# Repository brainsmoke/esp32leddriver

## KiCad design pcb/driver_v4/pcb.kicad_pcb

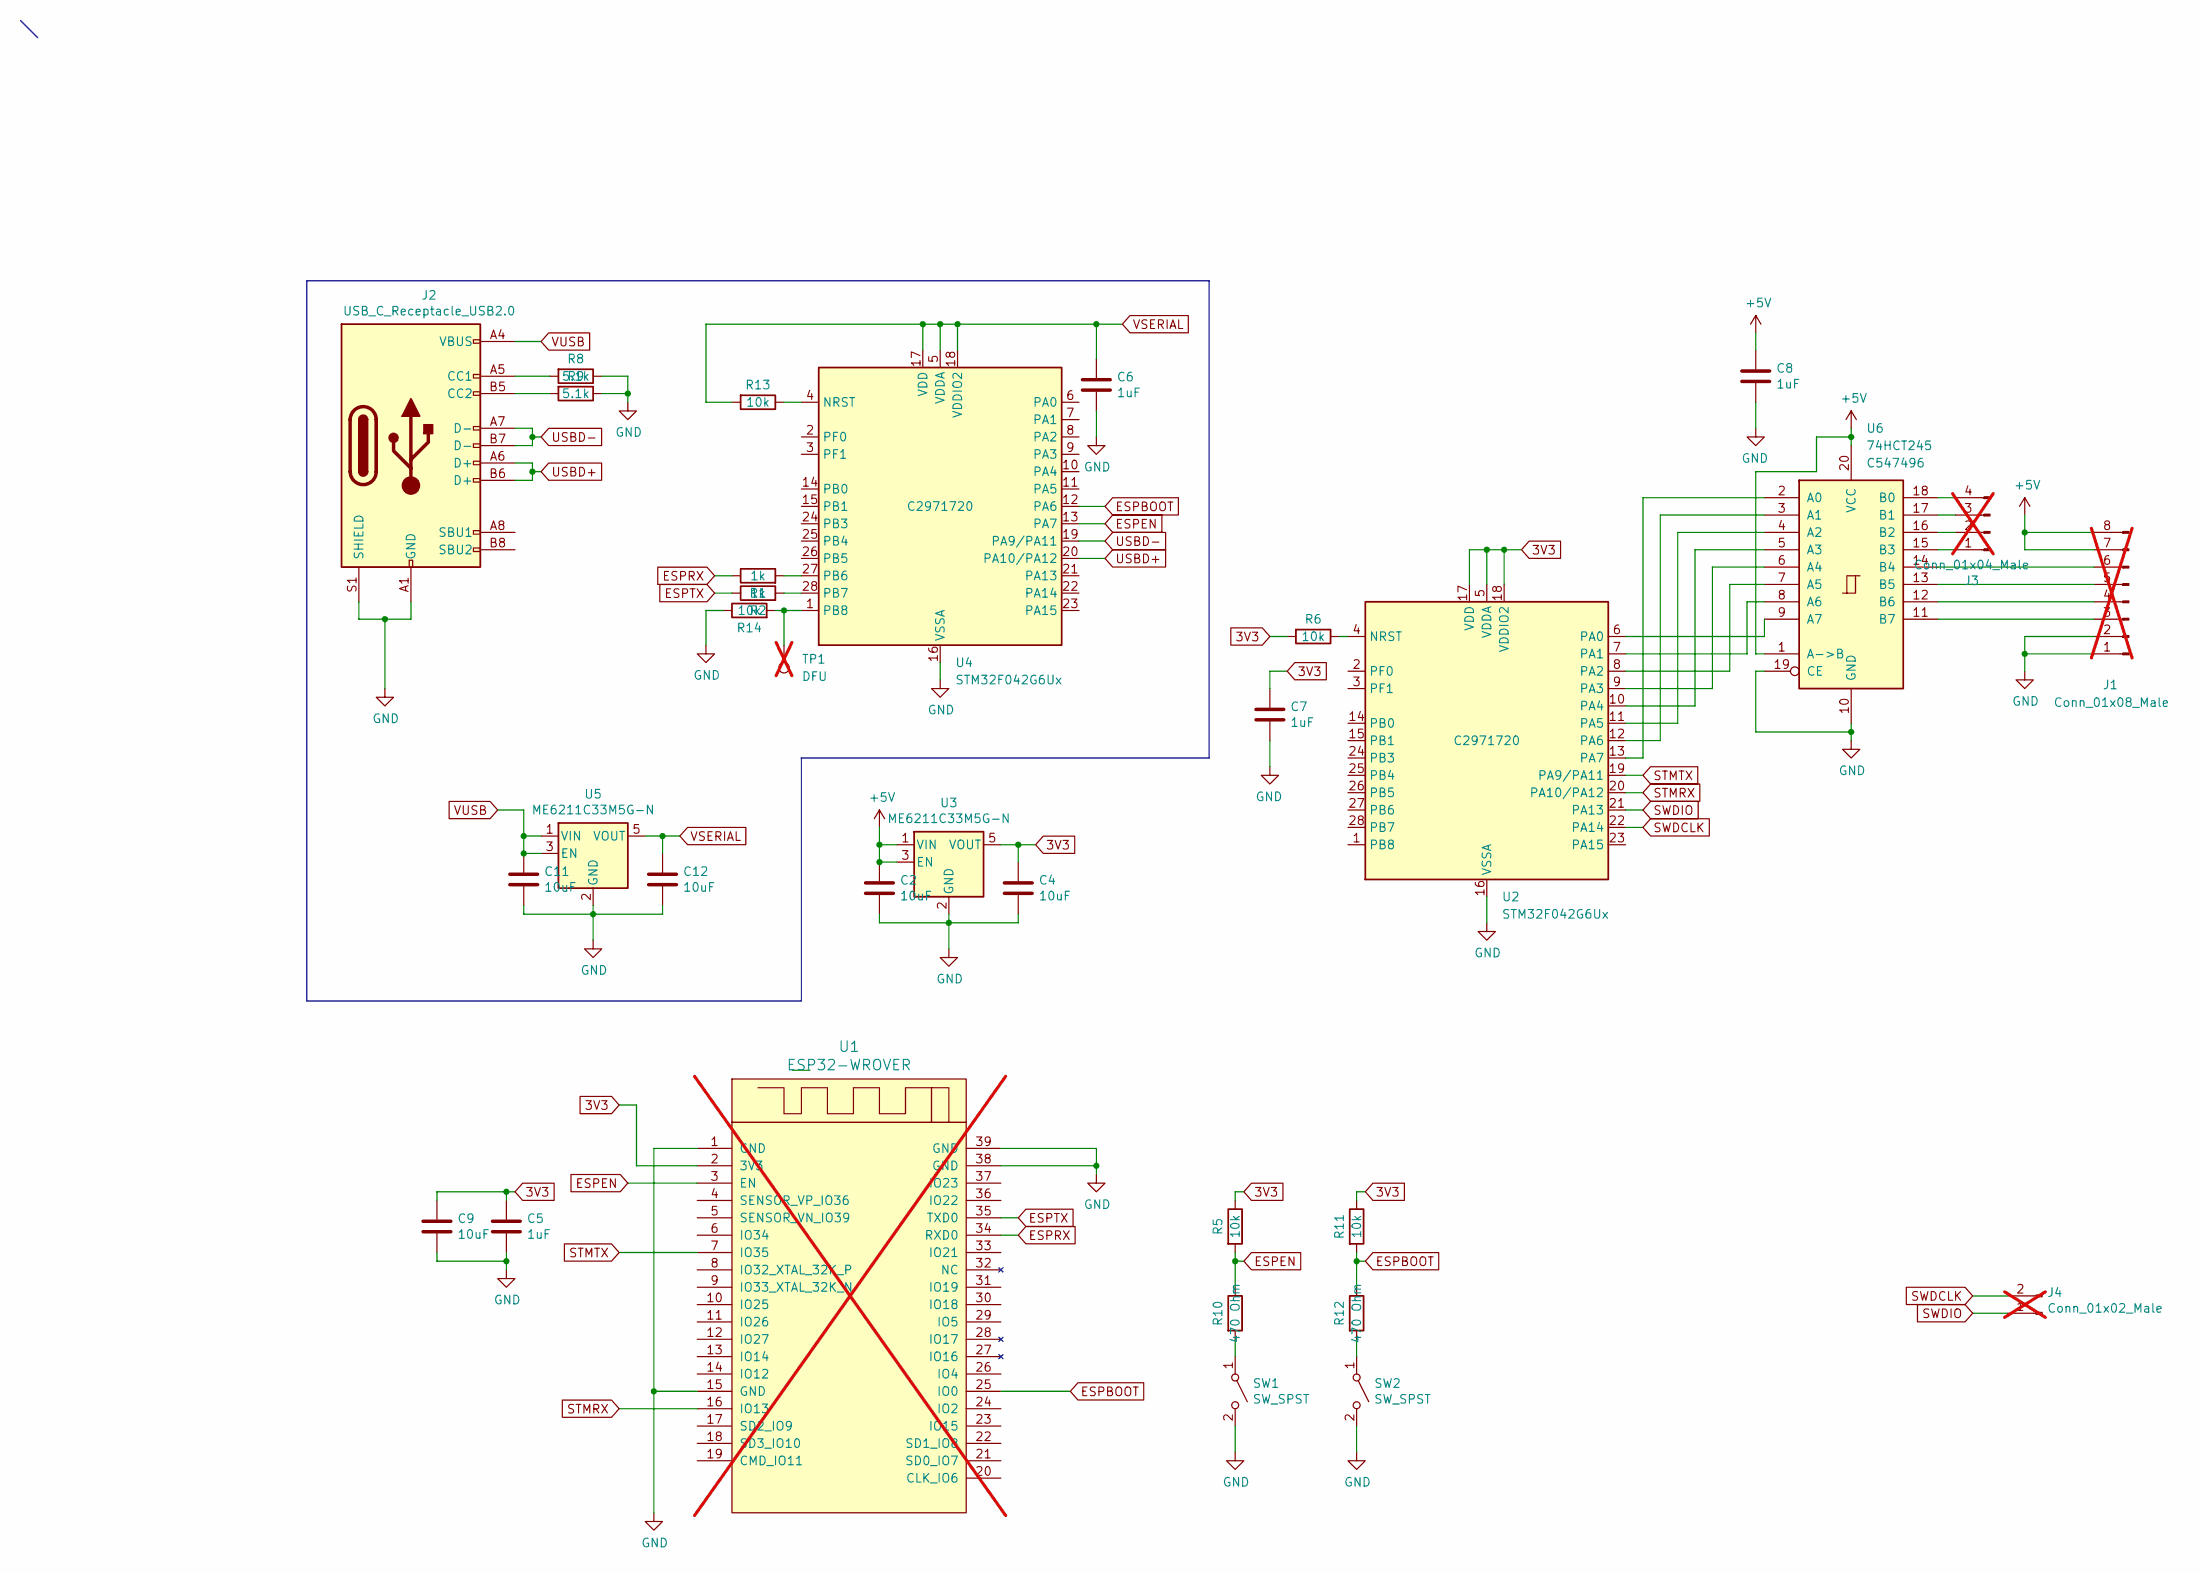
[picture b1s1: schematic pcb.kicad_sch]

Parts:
C2, C4, C9, C11, C12: 10uF; C_0603_1608Metric; LCSC C19702
C5, C6, C7, C8: 1uF; C_0402_1005Metric; LCSC C52923
J1: Conn_01x08_Male; PinHeader_1x08_P2.54mm_Vertical; not fitted
J2: USB_C_Receptacle_USB2.0; USB_C_Receptacle_HRO_TYPE-C-31-M-12; LCSC C165948
J3: Conn_01x04_Male; PinHeader_1x04_P2.54mm_Vertical; not fitted
J4: Conn_01x02_Male; PinHeader_1x02_P2.54mm_Vertical; not fitted
R1, R2: 1k; R_0402_1005Metric; LCSC C11702
R5, R6, R11, R13, R14: 10k; R_0402_1005Metric; LCSC C25744
R8, R9: 5.1k; R_0402_1005Metric; LCSC C25905
R10, R12: 470 Ohm; R_0402_1005Metric; LCSC C25117
SW1, SW2: SW_SPST; SW_Push_1P1T_NO_CK_KMR2; LCSC C318893
TP1: DFU; TestPoint_Pad_D1.0mm; not fitted
U1: ESP32-WROVER; XCVR_ESP32-WROVER; not fitted
U2, U4: STM32F042G6Ux; QFN-28_4x4mm_P0.5mm; LCSC C2971720
U3, U5: ME6211C33M5G-N; SOT-23-5; LCSC C82942
U6: 74HCT245; DHVQFN-20-1EP_2.5x4.5mm_P0.5mm_EP1x3mm; LCSC C547496

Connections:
3V3: C4.1, C5.1, C7.1, C9.1, R5.1, R6.2, R11.1, U1.2 (3V3), U2.5 (VDDA), U2.17 (VDD), U2.18 (VDDIO2), U3.5 (VOUT)
+5V: C2.1, C8.1, J1.7, J1.8, U3.1 (VIN), U3.3 (EN), U6.1 (A->B), U6.20 (VCC)
ESPBOOT: R11.2, R12.1, U1.25 (IO0), U4.12 (PA6)
ESPEN: R5.2, R10.1, U1.3 (EN), U4.13 (PA7)
ESPRX: R1.1, U1.34 (RXD0)
ESPTX: R2.1, U1.35 (TXD0)
GND: C2.2, C4.2, C5.2, C6.2, C7.2, C8.2, C9.2, C11.2, C12.2, J1.1, J1.2, J2.A1 (GND), J2.A12 (GND), J2.B1 (GND), J2.B12 (GND), J2.S1 (SHIELD), R8.1, R9.1, R14.1, SW1.2 (B), SW2.2 (B), U1.1 (GND), U1.15 (GND), U1.38 (GND), U1.39 (GND), U2.16 (VSSA), U3.2 (GND), U4.16 (VSSA), U5.2 (GND), U6.10 (GND), U6.19 (CE)
unnamed: J1.3, U6.11 (B7)
unnamed: J1.4, U6.12 (B6)
unnamed: J1.5, U6.13 (B5)
unnamed: J1.6, U6.14 (B4)
unnamed: J2.A5 (CC1), R8.2
unnamed: J2.B5 (CC2), R9.2
unnamed: J3.1, U6.15 (B3)
unnamed: J3.2, U6.16 (B2)
unnamed: J3.3, U6.17 (B1)
unnamed: J3.4, U6.18 (B0)
unnamed: R10.2, SW1.1 (A)
unnamed: R12.2, SW2.1 (A)
unnamed: R6.1, U2.4 (NRST)
unnamed: U2.6 (PA0), U6.9 (A7)
unnamed: U2.7 (PA1), U6.8 (A6)
unnamed: U2.8 (PA2), U6.7 (A5)
unnamed: U2.9 (PA3), U6.6 (A4)
unnamed: U2.10 (PA4), U6.5 (A3)
unnamed: U2.11 (PA5), U6.4 (A2)
unnamed: U2.12 (PA6), U6.3 (A1)
unnamed: U2.13 (PA7), U6.2 (A0)
unnamed: R13.1, U4.4 (NRST)
unnamed: R1.2, U4.27 (PB6)
unnamed: R2.2, U4.28 (PB7)
unnamed: R14.2, TP1.1, U4.1 (PB8)
STMRX: U1.16 (IO13), U2.20 (PA10/PA12)
STMTX: U1.7 (IO35), U2.19 (PA9/PA11)
SWDCLK: J4.2, U2.22 (PA14)
SWDIO: J4.1, U2.21 (PA13)
USBD+: J2.A6 (D+), J2.B6 (D+), U4.20 (PA10/PA12)
USBD-: J2.A7 (D-), J2.B7 (D-), U4.19 (PA9/PA11)
VSERIAL: C6.1, C12.1, R13.2, U4.5 (VDDA), U4.17 (VDD), U4.18 (VDDIO2), U5.5 (VOUT)
VUSB: C11.1, J2.A4 (VBUS), J2.A9 (VBUS), J2.B4 (VBUS), J2.B9 (VBUS), U5.1 (VIN), U5.3 (EN)

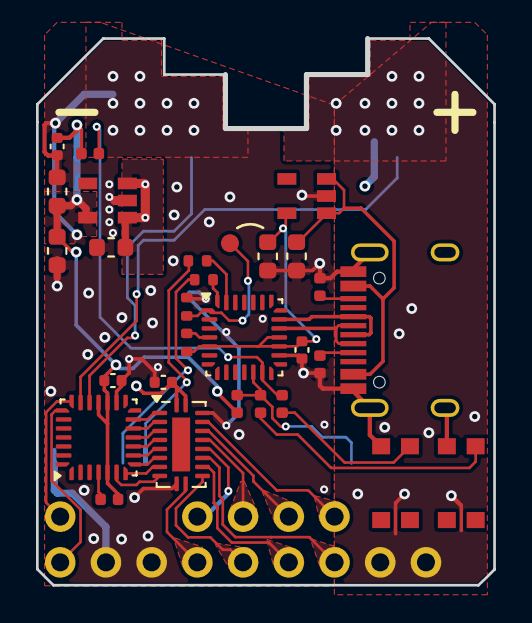
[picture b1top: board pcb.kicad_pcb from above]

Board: 4 copper layers, 25.4 x 30.4 mm, 33 parts (1 on the bottom side), 40 nets.

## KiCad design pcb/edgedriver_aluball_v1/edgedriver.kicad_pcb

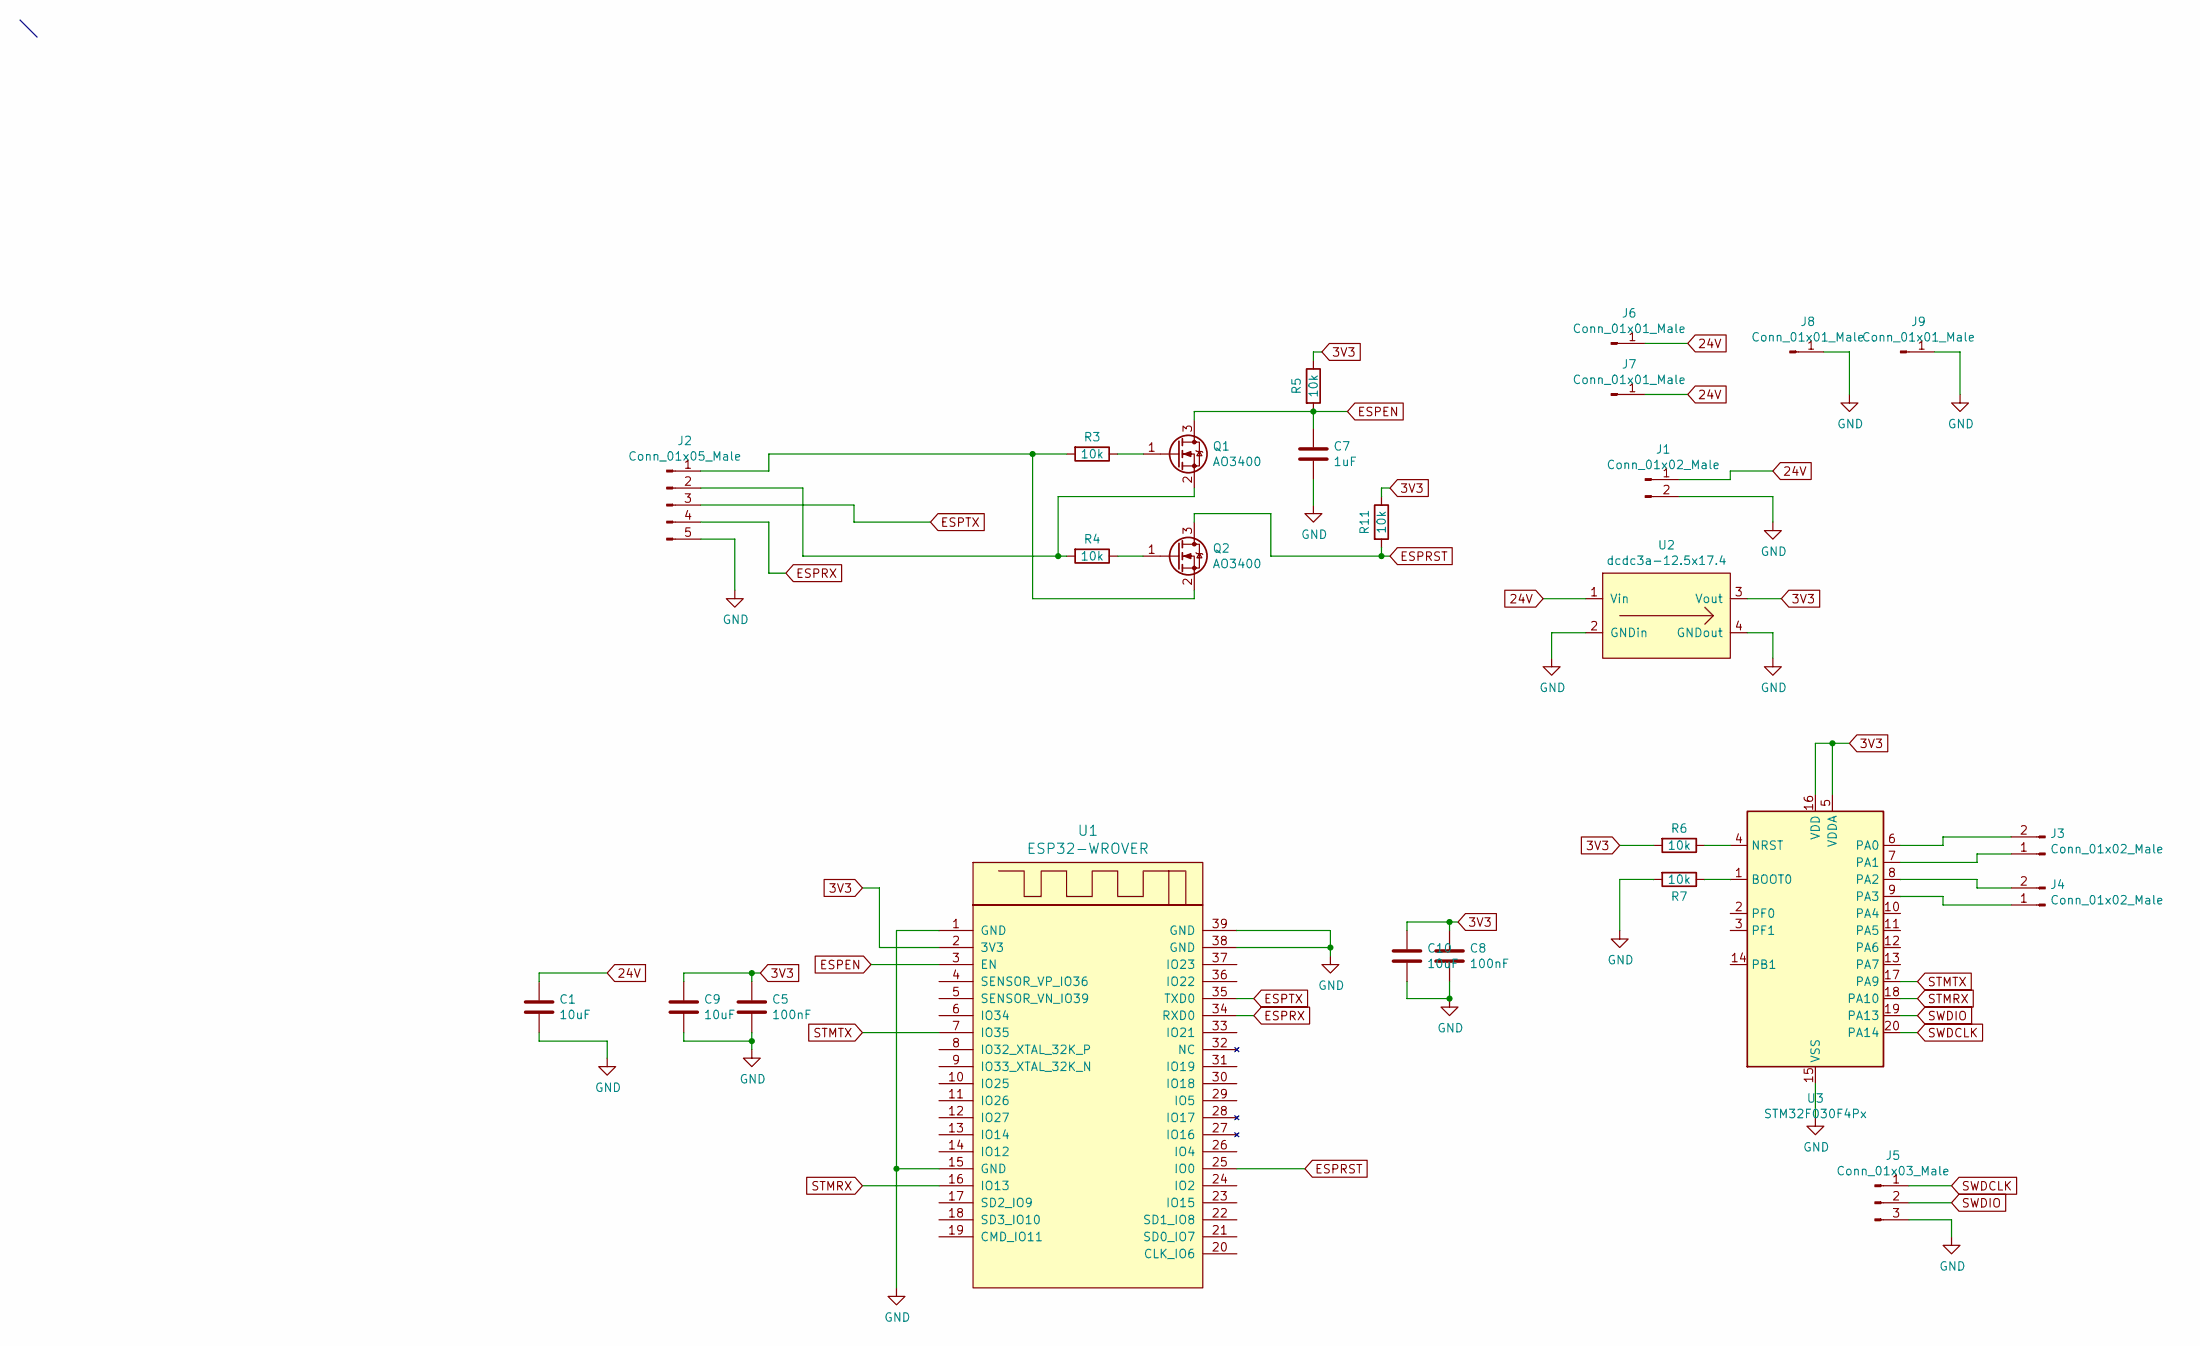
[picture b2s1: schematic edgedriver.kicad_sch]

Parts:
C1, C9, C10: 10uF; C_1206_3216Metric; LCSC C13585
C5, C8: 100nF; C_0402_1005Metric; LCSC C1525
C7: 1uF; C_0402_1005Metric; LCSC C52923
J1: Conn_01x02_Male; xt60-pcb
J2: Conn_01x05_Male; Molex_PicoBlade_53261-0571_1x05-1MP_P1.25mm_Horizontal; LCSC C225114
J3, J4: Conn_01x02_Male; PinHeader_1x02_P2.54mm_Vertical
J5: Conn_01x03_Male; PinHeader_1x03_P2.54mm_Vertical
J6, J7, J8, J9: Conn_01x01_Male; solderpad1
Q1, Q2: AO3400; SOT-23; LCSC C20917
R3, R4, R5, R6, R7, R11: 10k; R_0402_1005Metric; LCSC C25744
U1: ESP32-WROVER; XCVR_ESP32-WROVER; LCSC C701352
U2: dcdc3a-12.5x17.4
U3: STM32F030F4Px; TSSOP-20_4.4x6.5mm_P0.65mm; LCSC C89040

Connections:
3V3: C5.1, C8.1, C9.1, C10.1, R5.1, R6.2, R11.1, U1.2 (3V3), U2.3 (Vout), U3.5 (VDDA), U3.16 (VDD)
24V: C1.1, J1.1, J6.1, J7.1, U2.1 (Vin)
ESPEN: C7.1, Q1.3 (D), R5.2, U1.3 (EN)
ESPRST: Q2.3 (D), R11.2, U1.25 (IO0)
ESPRX: J2.4, U1.34 (RXD0)
ESPTX: J2.3, U1.35 (TXD0)
GND: C1.2, C5.2, C7.2, C8.2, C9.2, C10.2, J1.2, J2.5, J5.3, J8.1, J9.1, R7.2, U1.1 (GND), U1.15 (GND), U1.38 (GND), U1.39 (GND), U2.2 (GNDin), U2.4 (GNDout), U3.15 (VSS)
unnamed: J2.1, Q2.2 (S), R3.2
unnamed: J2.2, Q1.2 (S), R4.2
unnamed: J3.1, U3.7 (PA1)
unnamed: J3.2, U3.6 (PA0)
unnamed: J4.1, U3.9 (PA3)
unnamed: J4.2, U3.8 (PA2)
unnamed: Q1.1 (G), R3.1
unnamed: Q2.1 (G), R4.1
unnamed: R7.1, U3.1 (BOOT0)
unnamed: R6.1, U3.4 (NRST)
STMRX: U1.16 (IO13), U3.18 (PA10)
STMTX: U1.7 (IO35), U3.17 (PA9)
SWDCLK: J5.1, U3.20 (PA14)
SWDIO: J5.2, U3.19 (PA13)

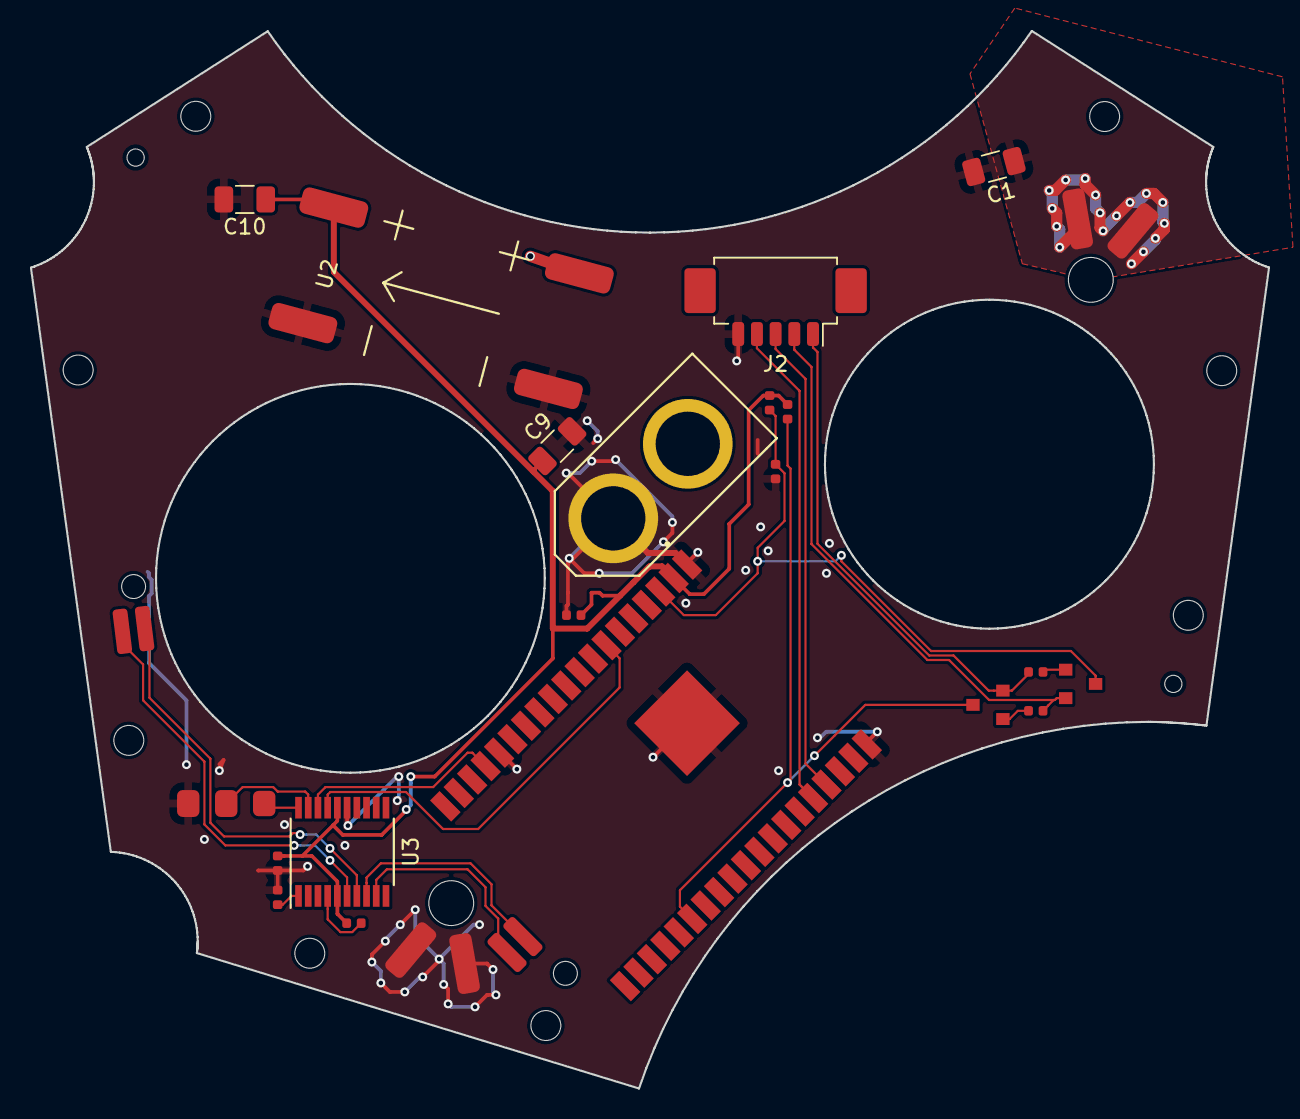
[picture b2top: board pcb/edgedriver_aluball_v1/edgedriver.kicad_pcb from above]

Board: 2 copper layers, 82.8 x 70.7 mm, 26 parts (0 on the bottom side), 21 nets.

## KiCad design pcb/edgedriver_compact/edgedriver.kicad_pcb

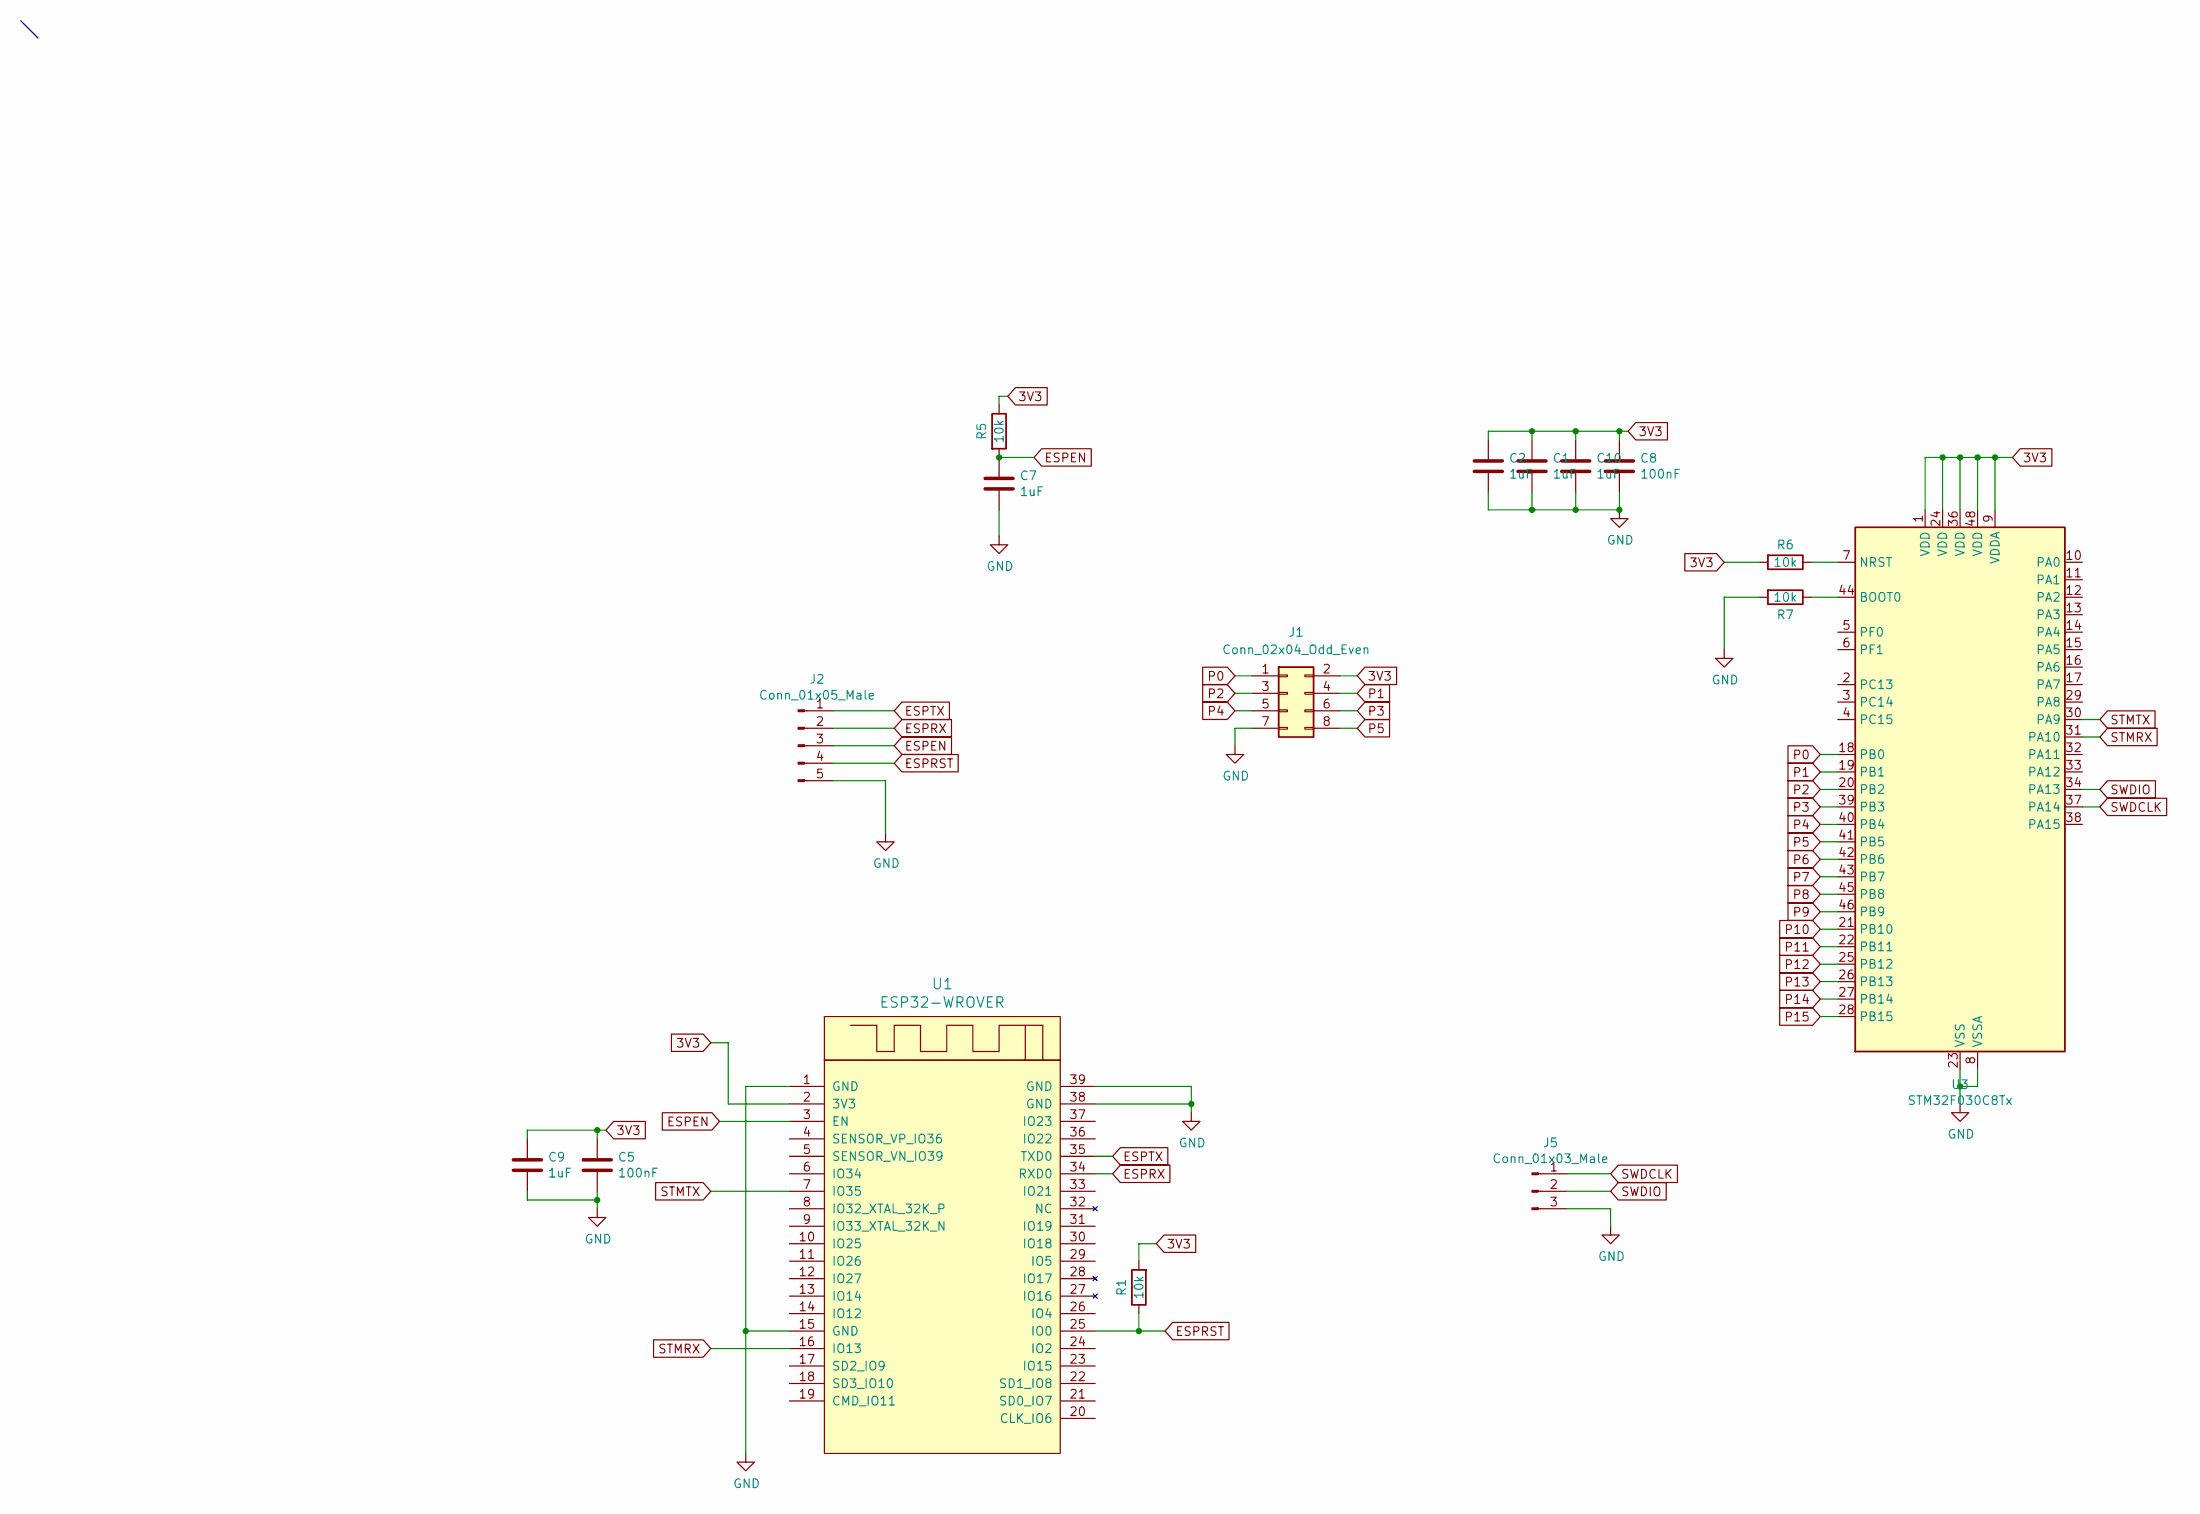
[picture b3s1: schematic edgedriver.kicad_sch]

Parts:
C1, C2, C7, C9, C10: 1uF; C_0402_1005Metric; LCSC C52923
C5, C8: 100nF; C_0402_1005Metric; LCSC C1525
J1: Conn_02x04_Odd_Even; PinSocket_2x04_P2.54mm_Vertical
J2: Conn_01x05_Male; Molex_PicoBlade_53261-0571_1x05-1MP_P1.25mm_Horizontal; LCSC C225114
J5: Conn_01x03_Male; PinHeader_1x03_P2.54mm_Vertical
R1, R5, R6, R7: 10k; R_0402_1005Metric; LCSC C25744
U1: ESP32-WROVER; XCVR_ESP32-WROVER; LCSC C701352
U3: STM32F030C8Tx; LQFP-48_7x7mm_P0.5mm; LCSC C23922

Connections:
3V3: C1.1, C2.1, C5.1, C8.1, C9.1, C10.1, J1.2, R1.2, R5.1, R6.2, U1.2 (3V3), U3.1 (VDD), U3.9 (VDDA), U3.24 (VDD), U3.36 (VDD), U3.48 (VDD)
ESPEN: C7.1, J2.3, R5.2, U1.3 (EN)
ESPRST: J2.4, R1.1, U1.25 (IO0)
ESPRX: J2.2, U1.34 (RXD0)
ESPTX: J2.1, U1.35 (TXD0)
GND: C1.2, C2.2, C5.2, C7.2, C8.2, C9.2, C10.2, J1.7, J2.5, J5.3, R7.2, U1.1 (GND), U1.15 (GND), U1.38 (GND), U1.39 (GND), U3.8 (VSSA), U3.23 (VSS), U3.35 (VSS), U3.47 (VSS)
unnamed: R7.1, U3.44 (BOOT0)
unnamed: R6.1, U3.7 (NRST)
P0: J1.1, U3.18 (PB0)
P1: J1.4, U3.19 (PB1)
P2: J1.3, U3.20 (PB2)
P3: J1.6, U3.39 (PB3)
P4: J1.5, U3.40 (PB4)
P5: J1.8, U3.41 (PB5)
P6: U3.42 (PB6)
P7: U3.43 (PB7)
P8: U3.45 (PB8)
P9: U3.46 (PB9)
P10: U3.21 (PB10)
P11: U3.22 (PB11)
P12: U3.25 (PB12)
P13: U3.26 (PB13)
P14: U3.27 (PB14)
P15: U3.28 (PB15)
STMRX: U1.16 (IO13), U3.31 (PA10)
STMTX: U1.7 (IO35), U3.30 (PA9)
SWDCLK: J5.1, U3.37 (PA14)
SWDIO: J5.2, U3.34 (PA13)

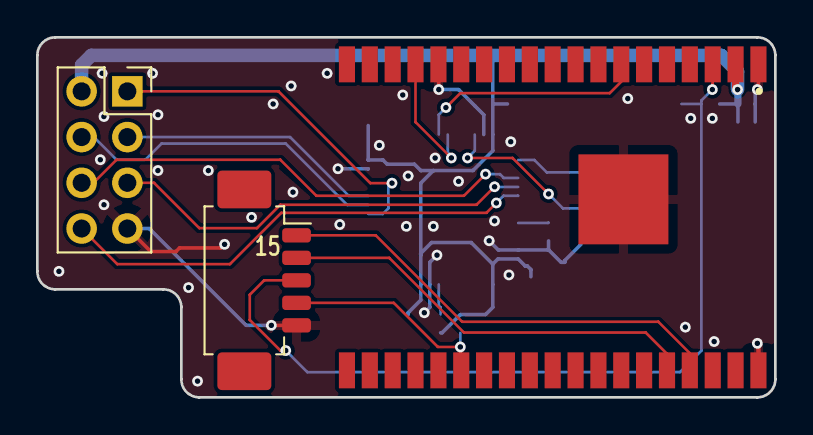
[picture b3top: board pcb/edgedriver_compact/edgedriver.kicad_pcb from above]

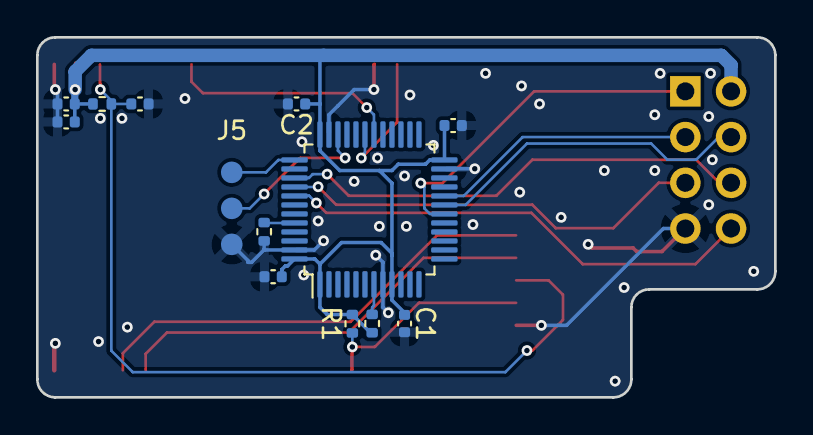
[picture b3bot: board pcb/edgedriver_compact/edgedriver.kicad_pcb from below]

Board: 4 copper layers, 41.0 x 20.0 mm, 16 parts (13 on the bottom side), 18 nets.

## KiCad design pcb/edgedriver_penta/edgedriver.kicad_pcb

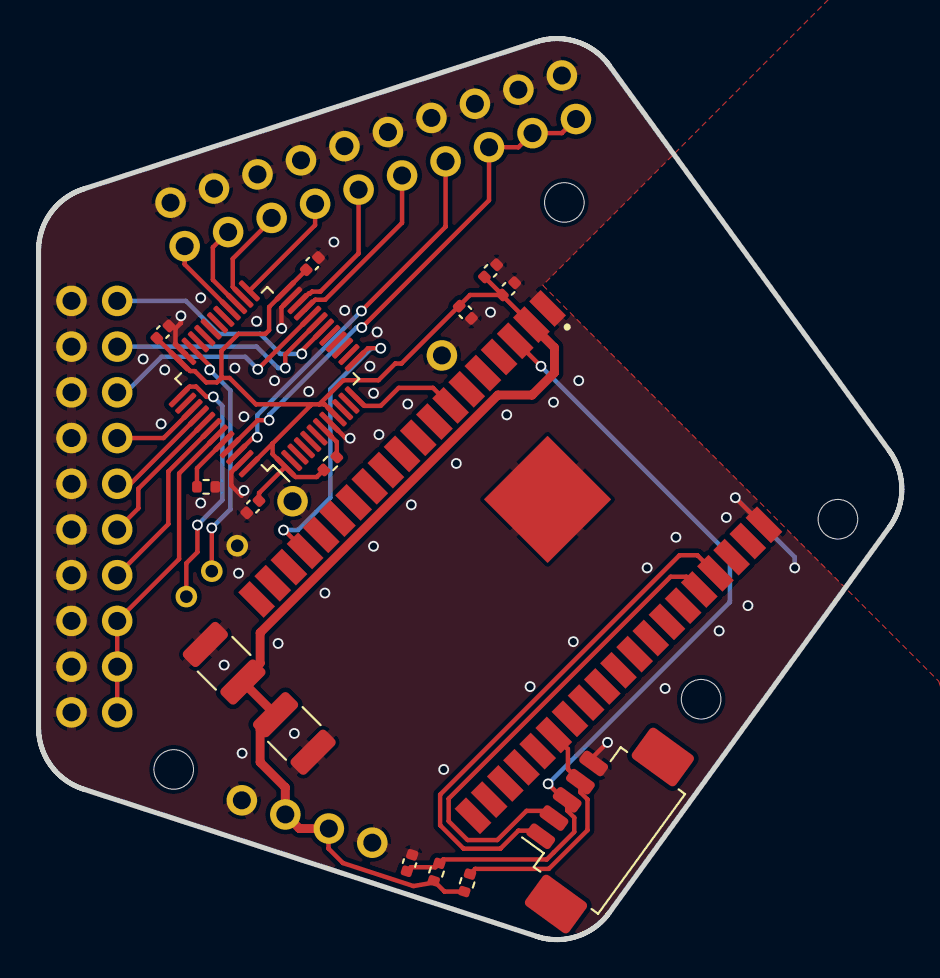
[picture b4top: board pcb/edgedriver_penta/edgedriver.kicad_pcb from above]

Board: 2 copper layers, 48.0 x 50.1 mm, 22 parts (0 on the bottom side), 28 nets.

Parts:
C1, C4: 22uF; C_1210_3225Metric
C2, C3, C7, C9, C10: 1uF; C_0402_1005Metric
C5, C8: 100nF; C_0402_1005Metric
J1, J3: Conn_02x10_Odd_Even; PinHeader_2x10_P2.54mm_Vertical
J2: Conn_01x05_Male; Molex_PicoBlade_53261-0571_1x05-1MP_P1.25mm_Horizontal
J4: Conn_01x04_Male; PinHeader_1x04_P2.54mm_Vertical
J5: Conn_01x03_Male; PinHeader_1x03_P2.54mm_Vertical
J6, J7: Conn_01x01_Male; PinHeader_1x01_P2.54mm_Vertical
R5, R6, R7, R11: 10k; R_0402_1005Metric
U1: ESP32-WROVER; XCVR_ESP32-WROVER
U3: STM32F030C8Tx; LQFP-48_7x7mm_P0.5mm

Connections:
3V3: C1.1, C2.1, C3.1, C4.1, C5.1, C8.1, C9.1, C10.1, J4.2, J4.3, R5.1, R6.2, R11.1, U1.2 (3V3), U3.1 (VDD), U3.9 (VDDA), U3.24 (VDD), U3.36 (PF7), U3.48 (VDD)
DATA0: J1.19, U3.18 (PB0)
DATA1: J1.17, U3.19 (PB1)
DATA2: J1.15, U3.20 (PB2)
DATA3: J1.13, U3.39 (PB3)
DATA4: J1.11, U3.40 (PB4)
DATA5: J1.9, U3.41 (PB5)
DATA6: J1.7, U3.42 (PB6)
DATA7: J1.1, J1.3, J1.5, U3.43 (PB7)
DATA8: J3.15, J3.17, J3.19, U3.45 (PB8)
DATA9: J3.13, U3.46 (PB9)
DATA10: J3.11, U3.21 (PB10)
DATA11: J3.9, U3.22 (PB11)
DATA12: J3.7, U3.25 (PB12)
DATA13: J3.5, U3.26 (PB13)
DATA14: J3.3, U3.27 (PB14)
DATA15: J3.1, U3.28 (PB15)
ESPEN: C7.1, J2.3, R5.2, U1.3 (EN)
ESPRST: J2.4, R11.2, U1.25 (IO0)
ESPRX: J2.2, U1.34 (RXD0)
ESPTX: J2.1, U1.35 (TXD0)
GND: C1.2, C2.2, C3.2, C4.2, C5.2, C7.2, C8.2, C9.2, C10.2, J1.2, J1.4, J1.6, J1.8, J1.10, J1.12, J1.14, J1.16, J1.18, J1.20, J2.5, J3.2, J3.4, J3.6, J3.8, J3.10, J3.12, J3.14, J3.16, J3.18, J3.20, J4.1, J4.4, J5.3, J6.1, J7.1, R7.2, U1.1 (GND), U1.15 (GND), U1.38 (GND), U1.39 (GND), U3.8 (VSSA), U3.23 (VSS), U3.35 (PF6), U3.47 (VSS)
unnamed: R7.1, U3.44 (BOOT0)
unnamed: R6.1, U3.7 (NRST)
STMRX: U1.16 (IO13), U3.13 (PA3)
STMTX: U1.7 (IO35), U3.12 (PA2)
SWDCLK: J5.1, U3.37 (PA14)
SWDIO: J5.2, U3.34 (PA13)

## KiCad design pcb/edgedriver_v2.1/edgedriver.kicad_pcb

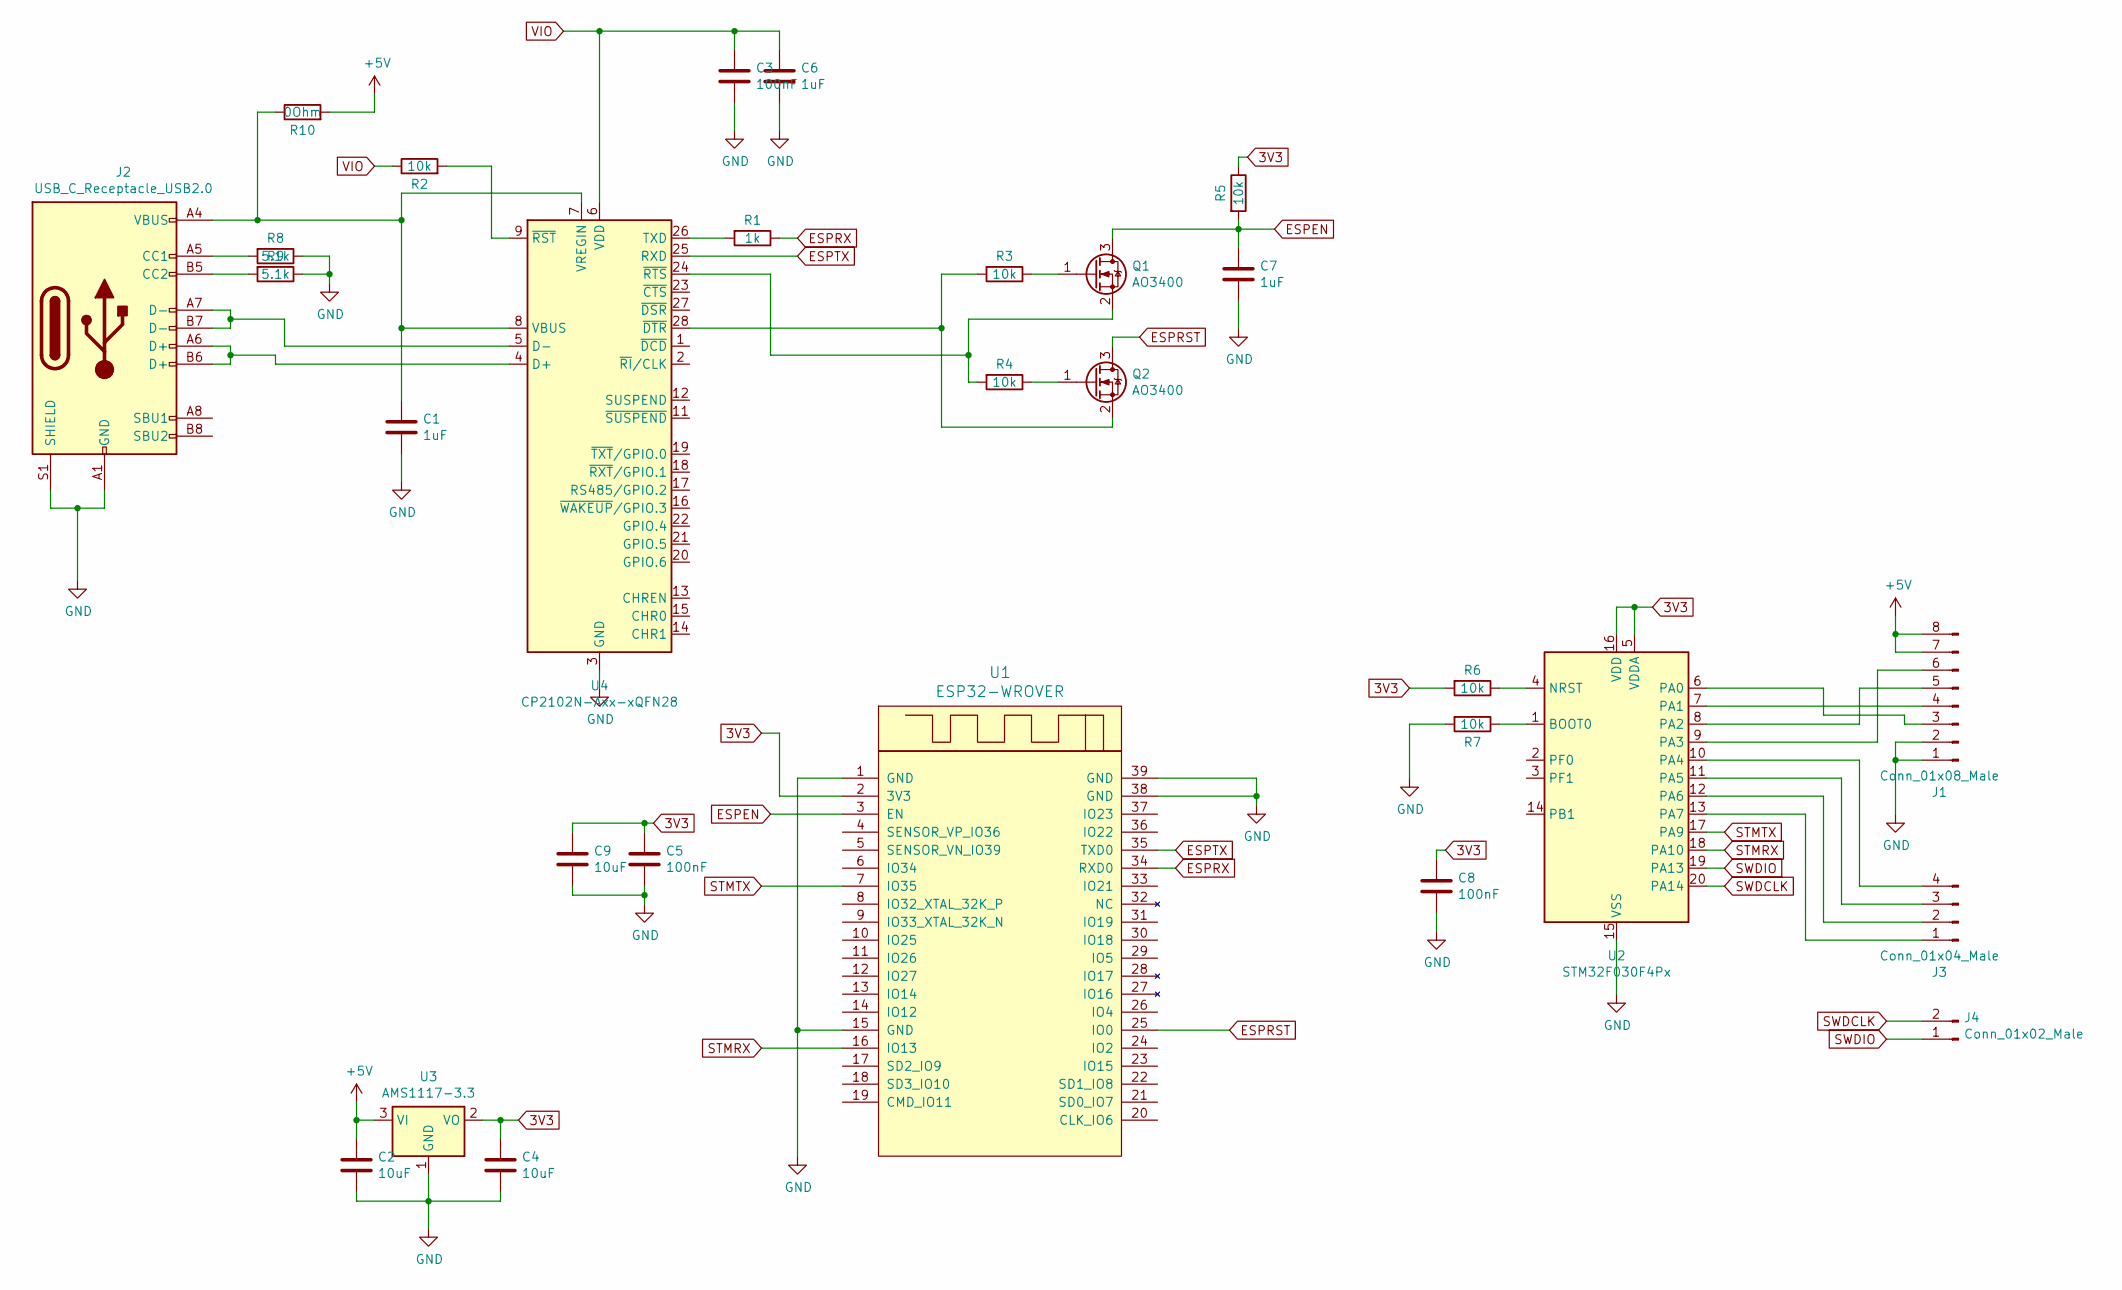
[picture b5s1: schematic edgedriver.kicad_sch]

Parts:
C1, C6, C7: 1uF; C_0603_1608Metric; LCSC C15849
C2, C4: 10uF; C_0603_1608Metric; LCSC C15850
C3, C5, C8: 100nF; C_0603_1608Metric; LCSC C14663
C9: 10uF; C_0603_1608Metric; LCSC C19702
J1: Conn_01x08_Male; PinHeader_1x08_P2.54mm_Vertical
J2: USB_C_Receptacle_USB2.0; USB_C_Receptacle_HRO_TYPE-C-31-M-12
J3: Conn_01x04_Male; PinHeader_1x04_P2.54mm_Vertical
J4: Conn_01x02_Male; PinHeader_1x02_P2.54mm_Vertical
Q1, Q2: AO3400; SOT-23; LCSC C20917
R1: 1k; R_0603_1608Metric_nolabel; LCSC C21190
R2, R3, R4, R5, R6, R7: 10k; R_0603_1608Metric_nolabel; LCSC C25804
R8, R9: 5.1k; R_0603_1608Metric_nolabel; LCSC C23186
R10: 0Ohm; R_0603_1608Metric_nolabel; LCSC C25804
U1: ESP32-WROVER; XCVR_ESP32-WROVER
U2: STM32F030F4Px; TSSOP-20_4.4x6.5mm_P0.65mm; LCSC C89040
U3: AMS1117-3.3; SOT-223-3_TabPin2; LCSC C6186
U4: CP2102N-Axx-xQFN28; QFN-28-1EP_5x5mm_P0.5mm_EP3.35x3.35mm; LCSC C6568

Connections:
3V3: C4.1, C5.1, C8.1, C9.1, R5.1, R6.2, U1.2 (3V3), U2.5 (VDDA), U2.16 (VDD), U3.2 (VO)
+5V: C2.1, J1.7, J1.8, R10.2, U3.3 (VI)
ESPEN: C7.1, Q1.3 (D), R5.2, U1.3 (EN)
ESPRST: Q2.3 (D), U1.25 (IO0)
ESPRX: R1.1, U1.34 (RXD0)
ESPTX: U1.35 (TXD0), U4.25 (RXD)
GND: C1.2, C2.2, C3.2, C4.2, C5.2, C6.2, C7.2, C8.2, C9.2, J1.1, J1.2, J2.A1 (GND), J2.A12 (GND), J2.B1 (GND), J2.B12 (GND), J2.S1 (SHIELD), R7.2, R8.1, R9.1, U1.1 (GND), U1.15 (GND), U1.38 (GND), U1.39 (GND), U2.15 (VSS), U3.1 (GND), U4.3 (GND), U4.29 (GND)
unnamed: J1.3, U2.6 (PA0)
unnamed: J1.4, U2.7 (PA1)
unnamed: J1.5, U2.8 (PA2)
unnamed: J1.6, U2.9 (PA3)
unnamed: J2.A5 (CC1), R8.2
unnamed: J2.B5 (CC2), R9.2
unnamed: J3.1, U2.13 (PA7)
unnamed: J3.2, U2.12 (PA6)
unnamed: J3.3, U2.11 (PA5)
unnamed: J3.4, U2.10 (PA4)
unnamed: Q1.1 (G), R3.1
unnamed: Q1.2 (S), R4.2, U4.24 (~RTS)
unnamed: Q2.1 (G), R4.1
unnamed: Q2.2 (S), R3.2, U4.28 (~DTR)
unnamed: R7.1, U2.1 (BOOT0)
unnamed: R6.1, U2.4 (NRST)
unnamed: J2.A6 (D+), J2.B6 (D+), U4.4 (D+)
unnamed: J2.A7 (D-), J2.B7 (D-), U4.5 (D-)
unnamed: R1.2, U4.26 (TXD)
unnamed: C1.1, J2.A4 (VBUS), J2.A9 (VBUS), J2.B4 (VBUS), J2.B9 (VBUS), R10.1, U4.7 (VREGIN), U4.8 (VBUS)
unnamed: R2.2, U4.9 (~RST)
STMRX: U1.16 (IO13), U2.18 (PA10)
STMTX: U1.7 (IO35), U2.17 (PA9)
SWDCLK: J4.2, U2.20 (PA14)
SWDIO: J4.1, U2.19 (PA13)
VIO: C3.1, C6.1, R2.1, U4.6 (VDD)

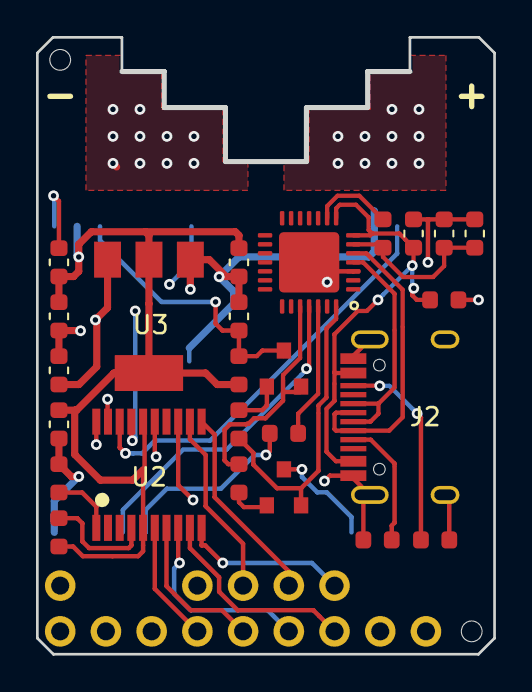
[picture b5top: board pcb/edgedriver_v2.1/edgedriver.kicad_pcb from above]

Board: 4 copper layers, 25.4 x 34.3 mm, 29 parts (1 on the bottom side), 33 nets.

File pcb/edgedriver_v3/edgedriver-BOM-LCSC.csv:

Comment,Designator,Footprint,LCSC Part Number
"10uF","C4,C2,C9","0603","C19702"
"1uF","C7,C6,C1","0603","C15849"
"100nF","C8,C5,C3","0603","C14663"
"AO3400","Q1,Q2","SOT-23-3L","C20917"
"1k","R1","0603","C21190"
"10k","R6,R7,R3,R4,R5,R2","0603","C25804"
"STM32F030F4P6","U2","TSSOP-20_4.4x6.5x0.65P","C89040"
"AMS1117-3.3","U3","SOT-223","C6186"
"CP2104","U4","QFN-24_EP_4.0x4.0x0.5P","C47742"
